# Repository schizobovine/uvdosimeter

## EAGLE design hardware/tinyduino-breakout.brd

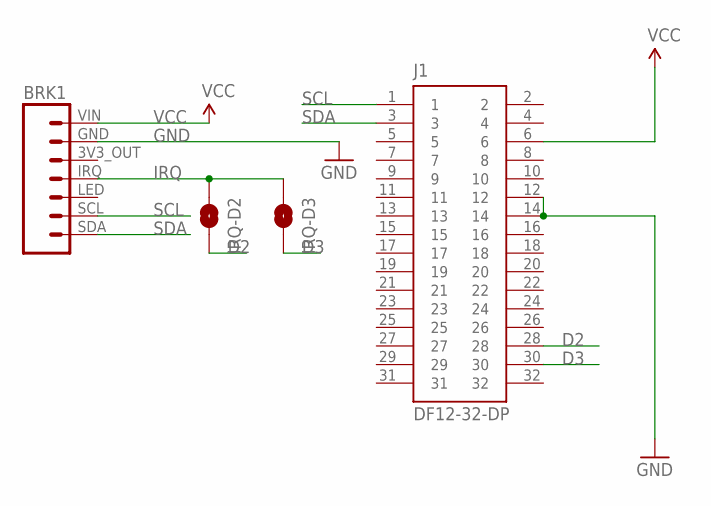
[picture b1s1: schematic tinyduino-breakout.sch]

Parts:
BRK1: ADAFRUIT-SI1145-BREAKOUT
IRQ-D2, IRQ-D3: JUMPER-PAD-2-NOYES_SILK; PAD-JUMPER-2-NO_YES_SILK
J1: DF12-32-DP

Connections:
D2: IRQ-D2.2, J1.28
D3: IRQ-D3.2, J1.30
GND: BRK1.GND, J1.12, J1.14
IRQ: BRK1.IRQ, IRQ-D2.1, IRQ-D3.1
SCL: BRK1.SCL, J1.1
SDA: BRK1.SDA, J1.3
VCC: BRK1.VIN, J1.6

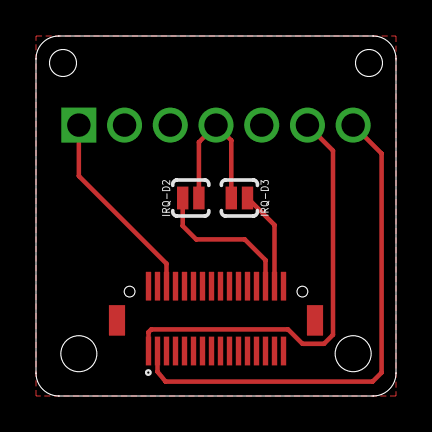
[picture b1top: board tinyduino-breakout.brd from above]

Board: 2 copper layers, 20.0 x 20.0 mm, 4 parts (1 on the bottom side), 7 nets.

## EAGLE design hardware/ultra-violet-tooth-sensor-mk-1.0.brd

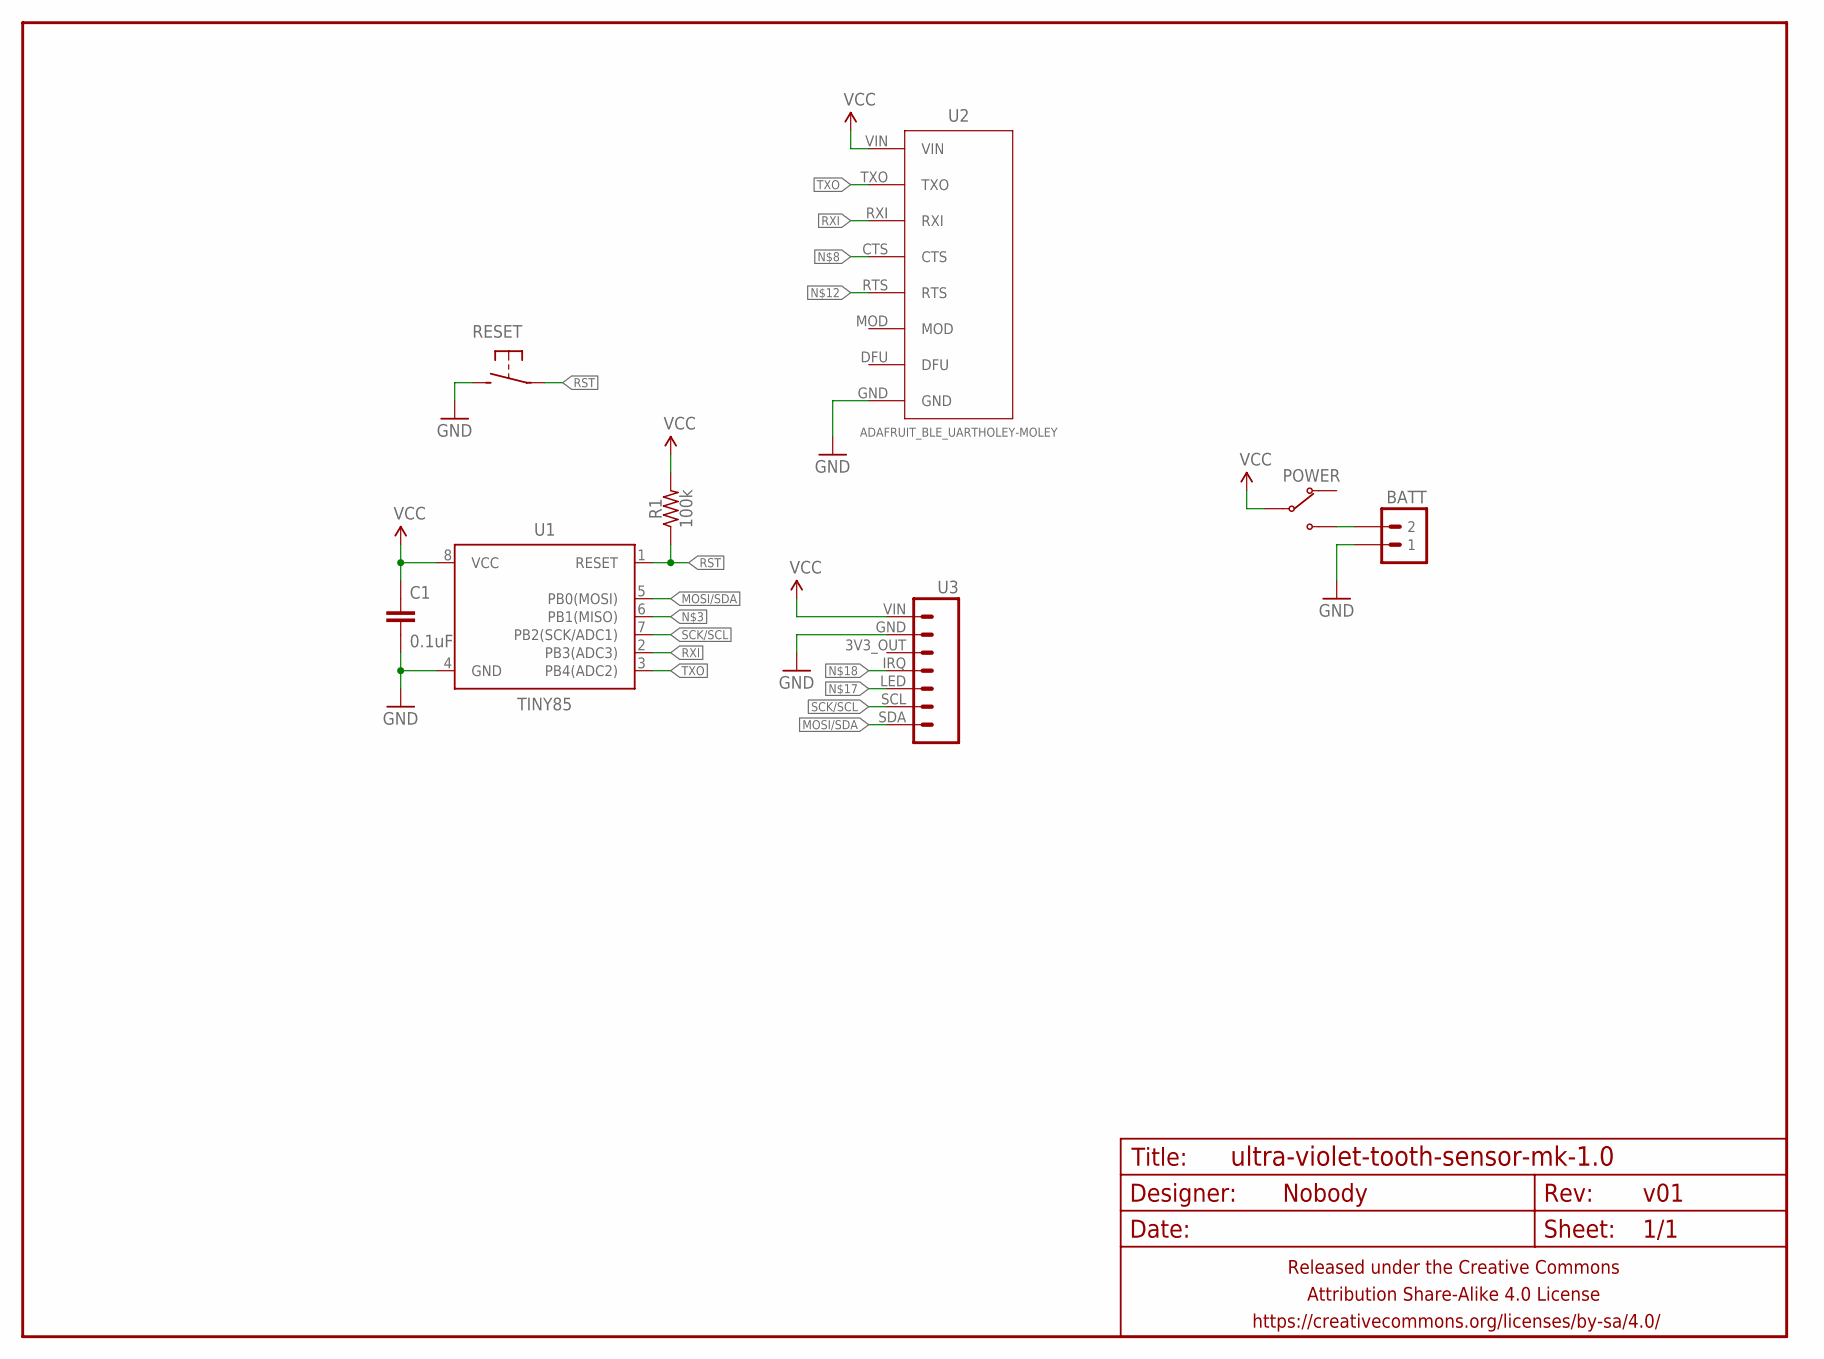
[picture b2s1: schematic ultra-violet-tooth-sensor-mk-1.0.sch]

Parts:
BATT: M02PTH-CENTERED-R+; 1X02-CENTER-R+
C1: 0.1uF; C025-024X044
FRAME1: FRAME-LETTERNO_PACKAGE; DUMMY
POWER: SWITCH-SPDTPTH-RA-2.54MM; SPDT-RA-2.54MM
R1: 100k; RESISTOR-AXIAL-PTH-7.62MM
RESET: SPST-NO-TACT3MM-RA; TACTILE-PTH-SIDE
U1: TINY85; DIP08
U2: ADAFRUIT_BLE_UARTHOLEY-MOLEY; ADAFRUIT_BLE_UART_HOLEY
U3: ADAFRUIT-SI1145-BREAKOUT

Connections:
GND: BATT.1, C1.2, RESET.2, U1.4 (GND), U2.GND, U3.GND
MOSI/SDA: U1.5 (PB0(MOSI)), U3.SDA
unnamed: BATT.2, POWER.3 (NO)
RST: R1.P$1 (1), RESET.1, U1.1 (RESET)
RXI: U1.2 (PB3(ADC3)), U2.RXI
SCK/SCL: U1.7 (PB2(SCK/ADC1)), U3.SCL
TXO: U1.3 (PB4(ADC2)), U2.TXO
VCC: C1.1, POWER.2 (COM), R1.P$2 (2), U1.8 (VCC), U2.VIN, U3.VIN

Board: 2 copper layers, 9 parts (2 on the bottom side), 8 nets, no tracks yet.

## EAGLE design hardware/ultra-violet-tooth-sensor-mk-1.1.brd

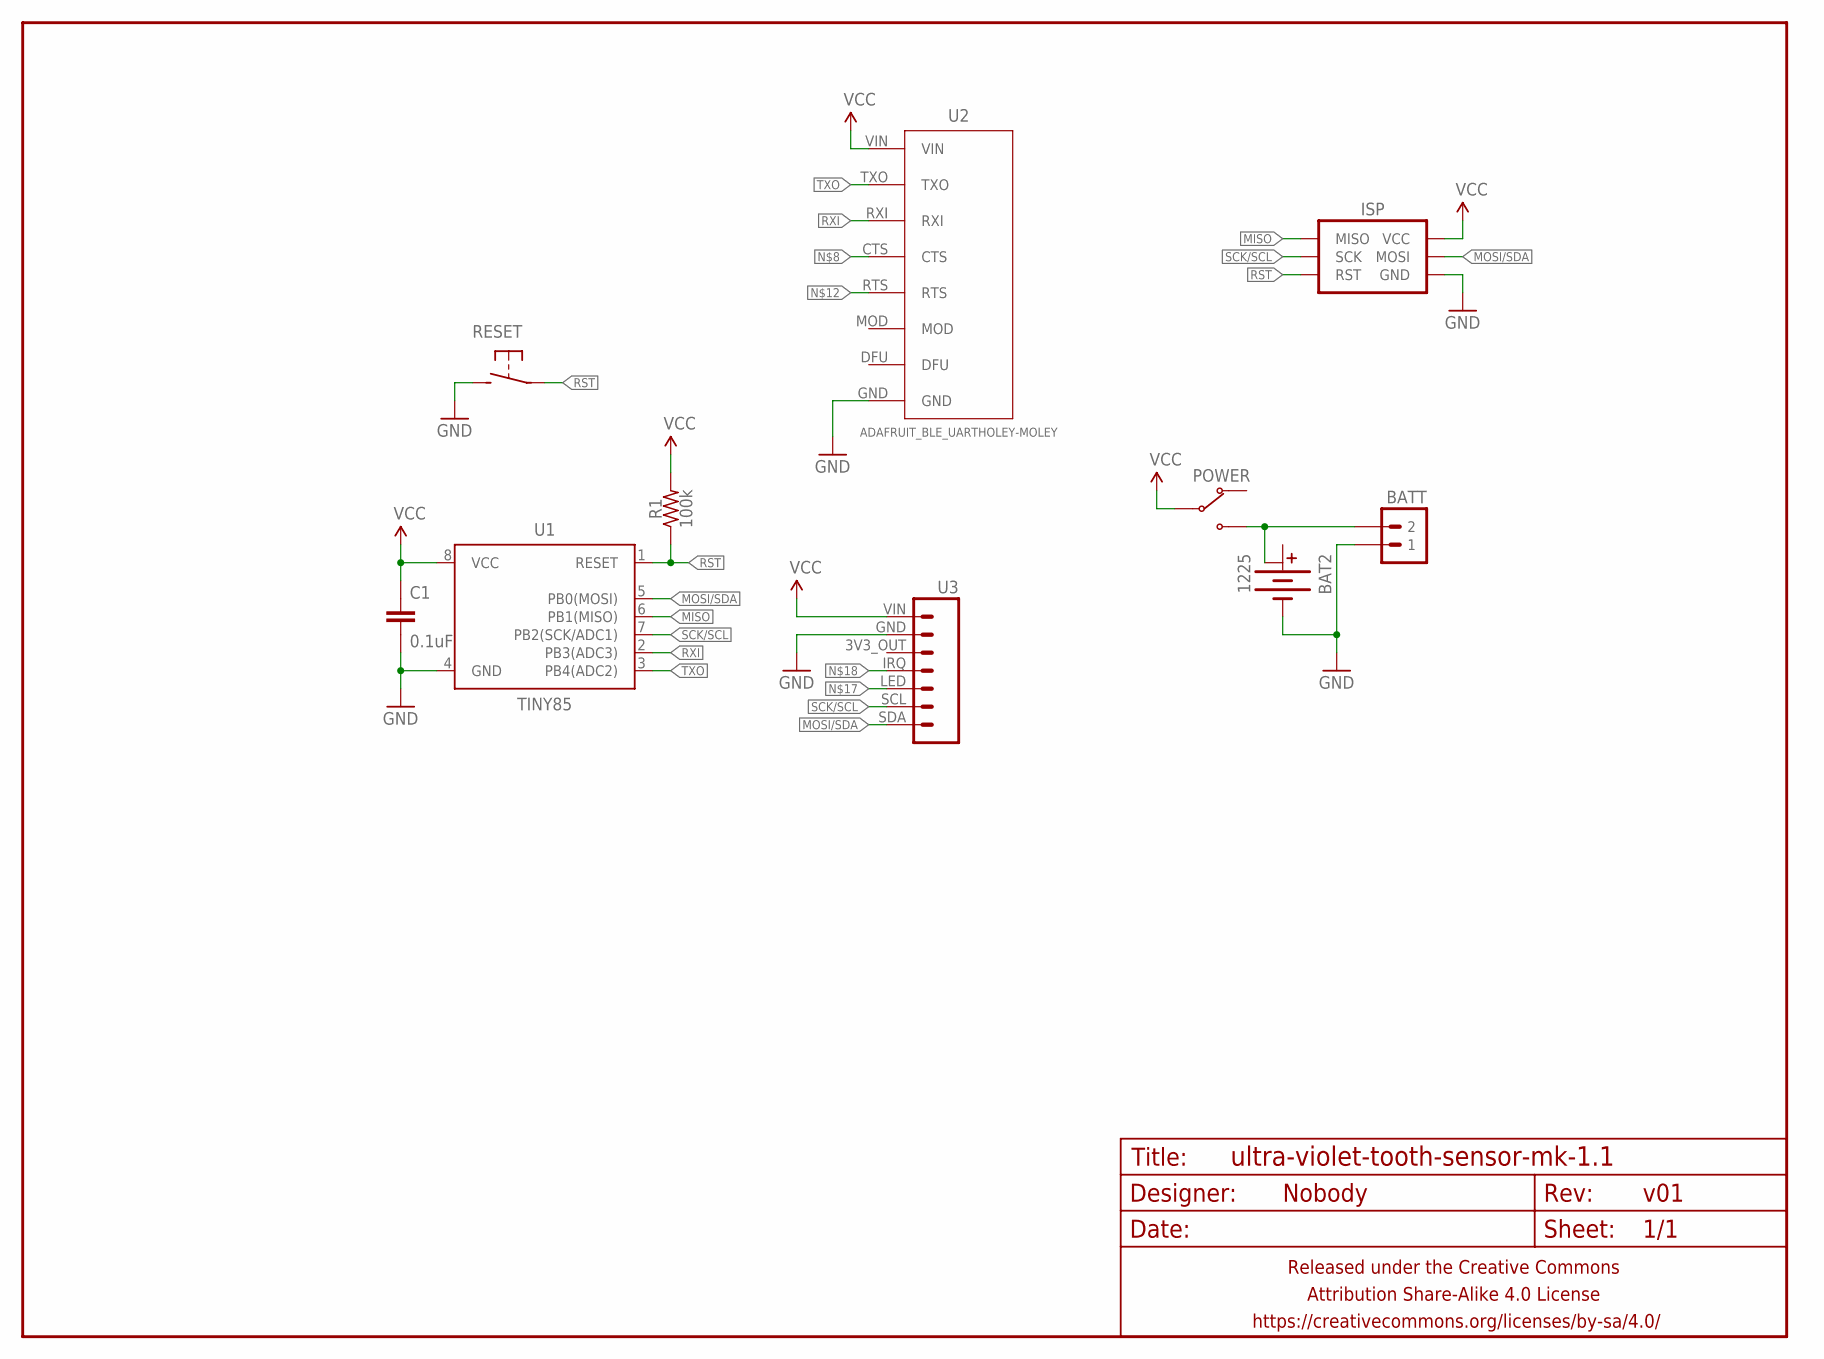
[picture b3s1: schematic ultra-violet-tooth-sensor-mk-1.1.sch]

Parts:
BAT2: 1225; BATTCON_12MM
BATT: M02PTH-CENTERED-R+; 1X02-CENTER-R+
C1: 0.1uF; C025-024X044
FRAME1: FRAME-LETTERNO_PACKAGE; DUMMY
ISP: AVR_SPI_PRG_6PTH; 2X3
POWER: SWITCH-SPDTPTH-RA-2.54MM; SPDT-RA-2.54MM
R1: 100k; RESISTOR-AXIAL-PTH-7.62MM
RESET: SPST-NO-TACT3MM-RA; TACTILE-PTH-SIDE
U1: TINY85; DIP08
U2: ADAFRUIT_BLE_UARTHOLEY-MOLEY; ADAFRUIT_BLE_UART_HOLEY
U3: ADAFRUIT-SI1145-BREAKOUT

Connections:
GND: BAT2.GND (-), BATT.1, C1.2, ISP.6 (GND), RESET.2, U1.4 (GND), U2.GND, U3.GND
MISO: ISP.1 (MISO), U1.6 (PB1(MISO))
MOSI/SDA: ISP.4 (MOSI), U1.5 (PB0(MOSI)), U3.SDA
unnamed: BAT2.PWR@2 (+1), BATT.2, POWER.3 (NO)
RST: ISP.5 (RST), R1.P$1 (1), RESET.1, U1.1 (RESET)
RXI: U1.2 (PB3(ADC3)), U2.RXI
SCK/SCL: ISP.3 (SCK), U1.7 (PB2(SCK/ADC1)), U3.SCL
TXO: U1.3 (PB4(ADC2)), U2.TXO
VCC: C1.1, ISP.2 (VCC), POWER.2 (COM), R1.P$2 (2), U1.8 (VCC), U2.VIN, U3.VIN

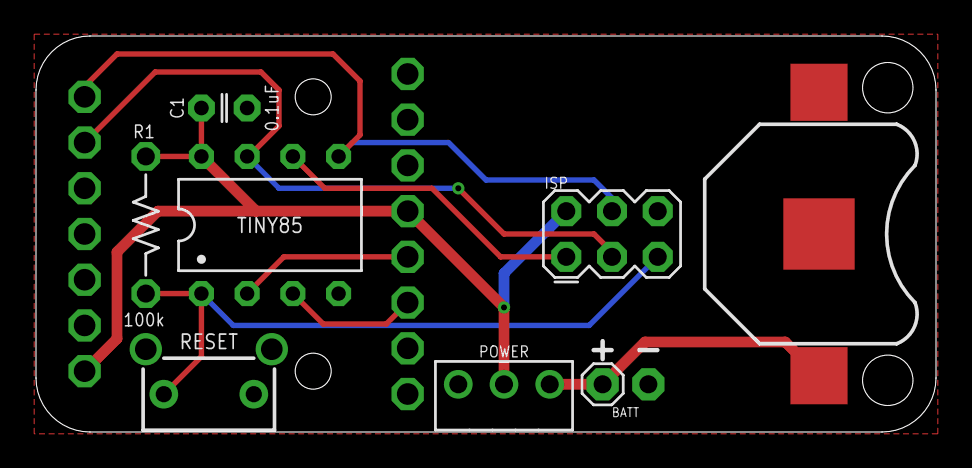
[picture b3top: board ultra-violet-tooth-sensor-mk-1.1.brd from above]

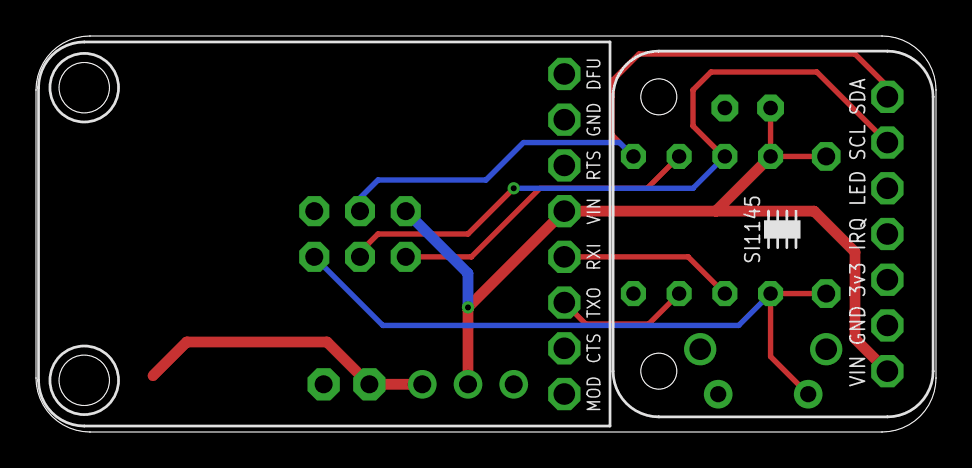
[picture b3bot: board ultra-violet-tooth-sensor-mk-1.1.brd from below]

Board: 2 copper layers, 50.0 x 22.0 mm, 11 parts (2 on the bottom side), 9 nets.

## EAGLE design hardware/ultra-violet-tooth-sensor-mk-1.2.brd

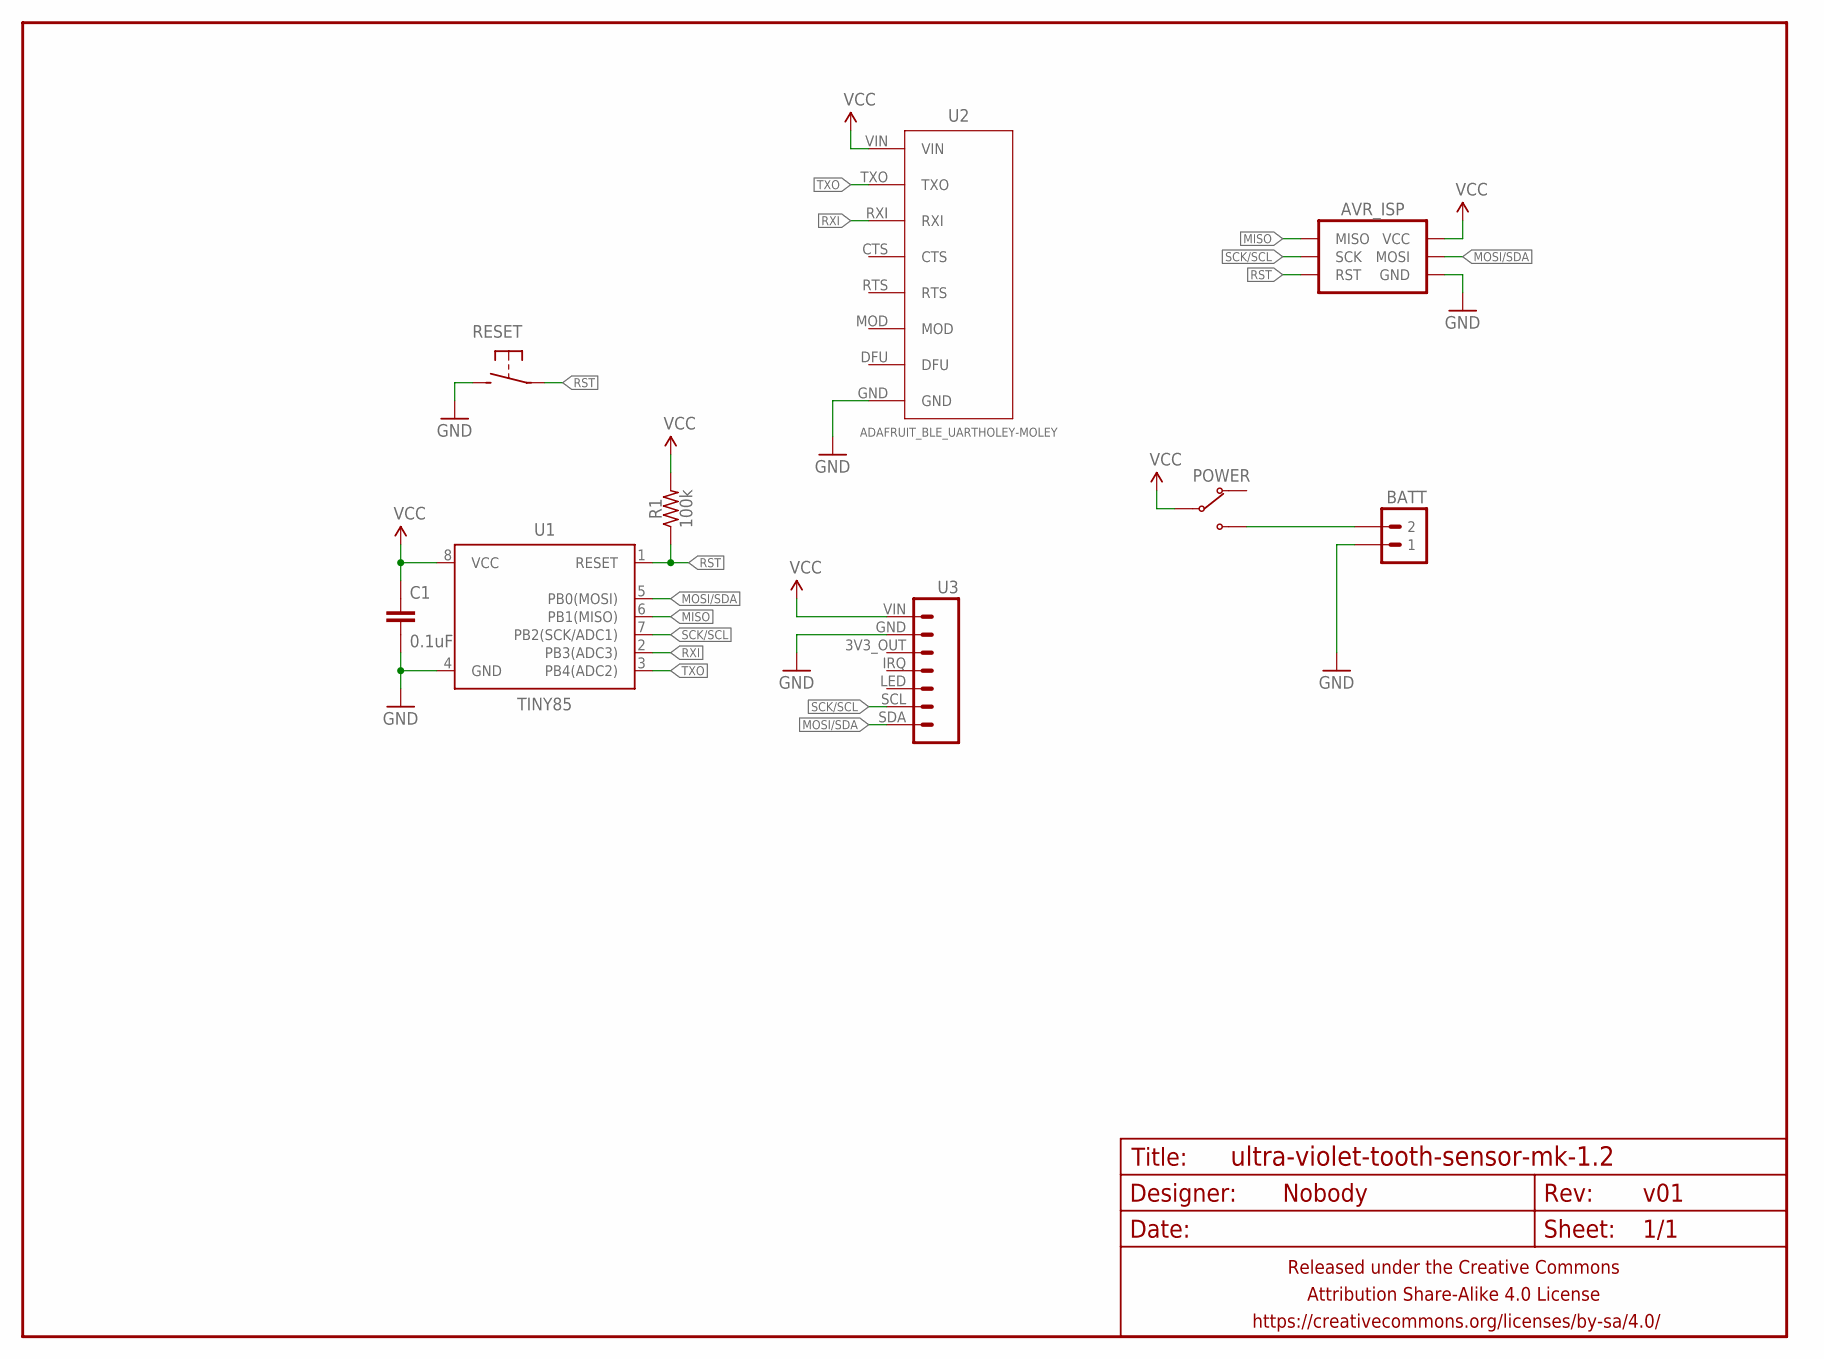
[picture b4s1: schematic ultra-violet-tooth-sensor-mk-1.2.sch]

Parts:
AVR_ISP: AVR_SPI_PRG_6PTH; 2X3
BATT: M02PTH-CENTERED-R+; 1X02-CENTER-R+
C1: 0.1uF; C025-024X044
FRAME1: FRAME-LETTERNO_PACKAGE; DUMMY
POWER: SWITCH-SPDTPTH-RA-2.54MM; SPDT-RA-2.54MM
R1: 100k; RESISTOR-AXIAL-PTH-6.35MM
RESET: SPST-NO-TACT3MM-RA; TACTILE-PTH-SIDE
U1: TINY85; DIP08
U2: ADAFRUIT_BLE_UARTHOLEY-MOLEY; ADAFRUIT_BLE_UART_HOLEY
U3: ADAFRUIT-SI1145-BREAKOUT

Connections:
GND: AVR_ISP.6 (GND), BATT.1, C1.2, RESET.2, U1.4 (GND), U2.GND, U3.GND
MISO: AVR_ISP.1 (MISO), U1.6 (PB1(MISO))
MOSI/SDA: AVR_ISP.4 (MOSI), U1.5 (PB0(MOSI)), U3.SDA
unnamed: BATT.2, POWER.3 (NO)
RST: AVR_ISP.5 (RST), R1.P$1 (1), RESET.1, U1.1 (RESET)
RXI: U1.2 (PB3(ADC3)), U2.RXI
SCK/SCL: AVR_ISP.3 (SCK), U1.7 (PB2(SCK/ADC1)), U3.SCL
TXO: U1.3 (PB4(ADC2)), U2.TXO
VCC: AVR_ISP.2 (VCC), C1.1, POWER.2 (COM), R1.P$2 (2), U1.8 (VCC), U2.VIN, U3.VIN

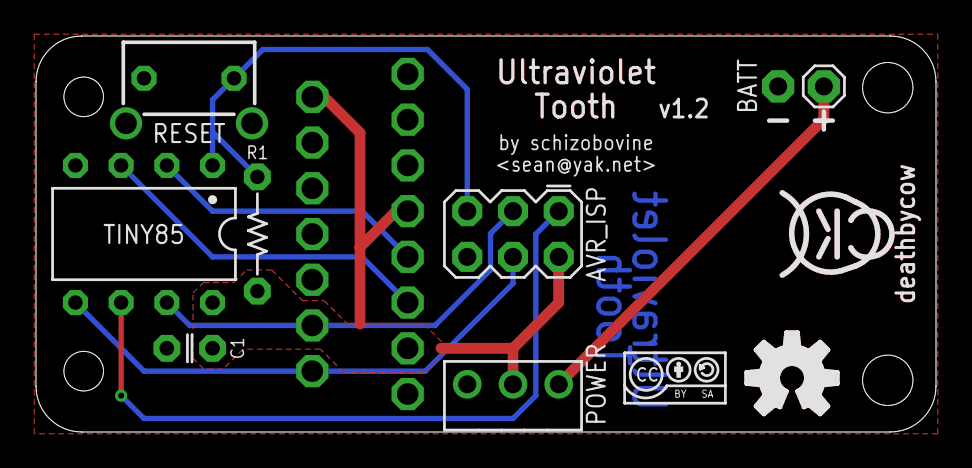
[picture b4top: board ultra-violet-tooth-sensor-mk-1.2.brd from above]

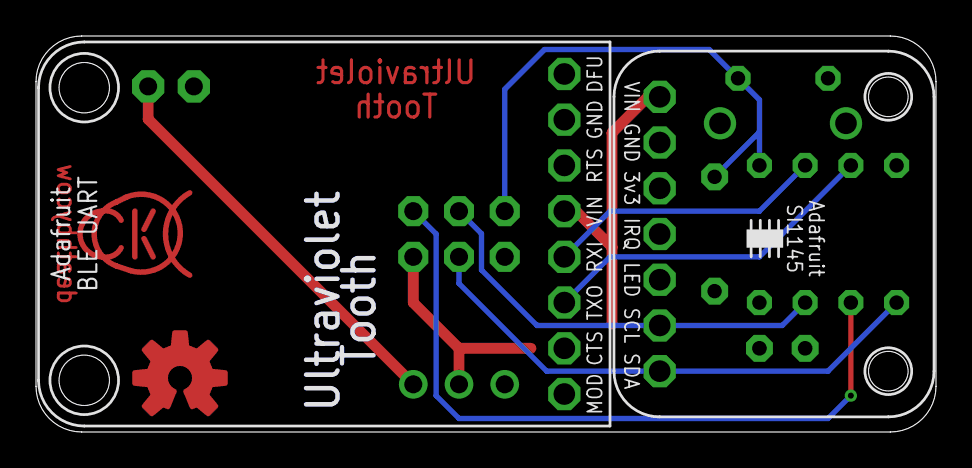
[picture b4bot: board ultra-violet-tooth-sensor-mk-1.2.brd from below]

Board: 2 copper layers, 50.0 x 22.0 mm, 13 parts (2 on the bottom side), 9 nets.

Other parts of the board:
U$1: CC-BY-SA-4.0-NO-URL
U$3: OSHWLOGO_TOP_0.2
U$4: COW_SMALL_METAL

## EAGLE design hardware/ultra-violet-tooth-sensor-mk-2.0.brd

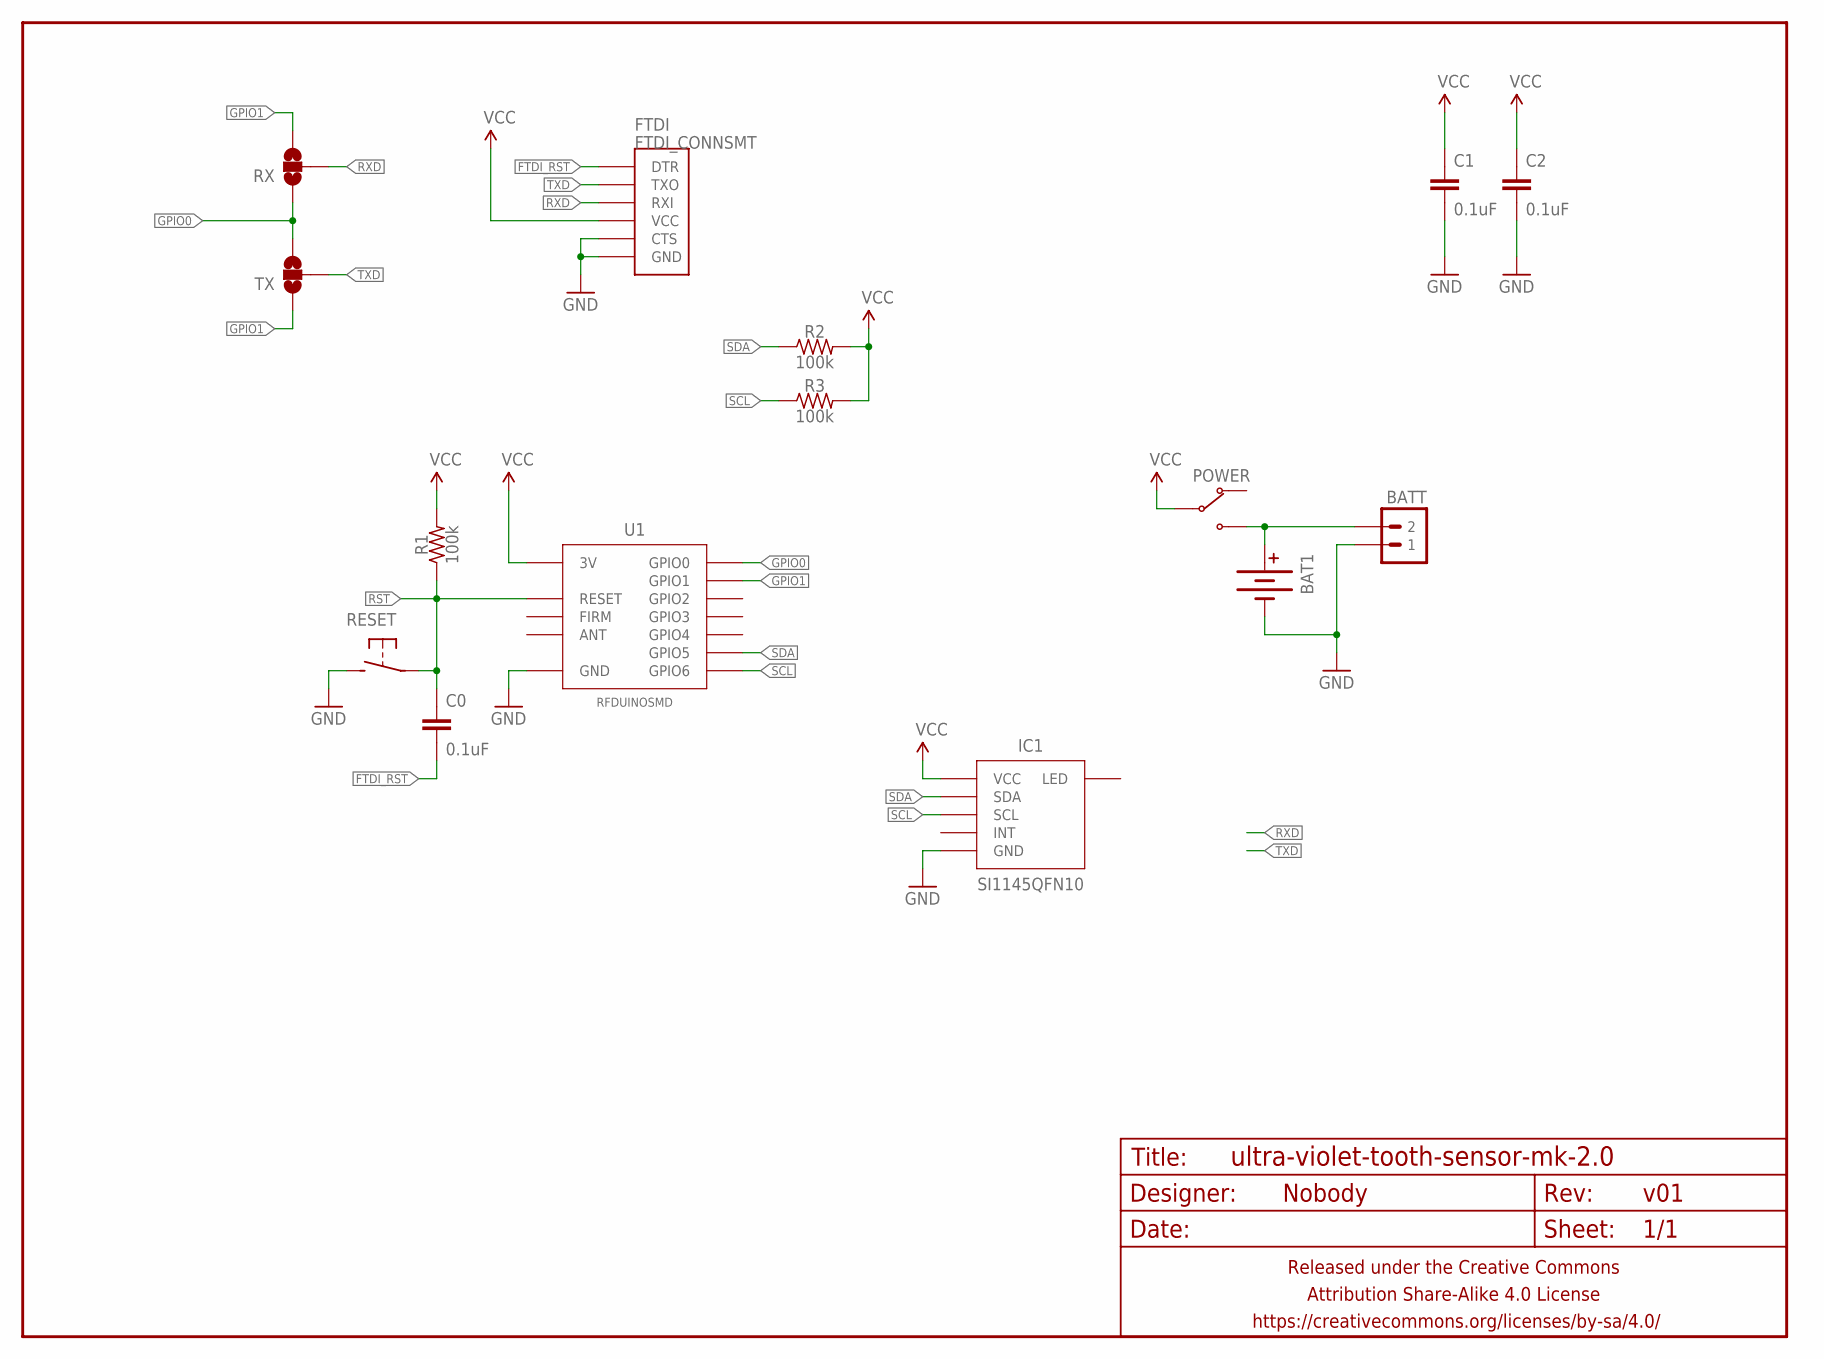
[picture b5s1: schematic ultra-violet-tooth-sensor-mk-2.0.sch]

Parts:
BAT1: BATTERY20MMSMD-MINE; BATTCON_20MM_MINE
BATT: M02PTH-CENTERED-R+; 1X02-CENTER-R+
C0, C1, C2: 0.1uF; C0805
FRAME1: FRAME-LETTERNO_PACKAGE; DUMMY
FTDI: FTDI_CONNSMT; FTDI_CONN_SMT
IC1: SI1145QFN10; SI1145
POWER: SWITCH-SPDTSMD-RA; SWITCH-SPDT-SMD-RA
R1, R2, R3: 100k; R0805
RESET: SPST-NO-TACTSMD-TINY; TACTILE-SWITCH-SMD
RX: JUMPER-PAD-3-NOFULL_BOX_SILK; PAD-JUMPER-3-NO_YES_SILK_FULL_BOX
TX: JUMPER-PAD-3-NOFULL_BOX_SILK; PAD-JUMPER-3-NO_YES_SILK_FULL_BOX
U1: RFDUINOSMD; RFDUINO-SMD

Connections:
FTDI_RST: C0.2, FTDI.DTR
GND: BAT1.BOTTOM (-), BATT.1, C1.2, C2.2, FTDI.CTS, FTDI.GND, IC1.GND, RESET.B@1 (2), RESET.B@2 (2), U1.GND@1 (GND), U1.GND@2 (GND), U1.GND@3 (GND), U1.GND@4 (GND), U1.GND@5 (GND), U1.GND@6 (GND), U1.GND@7 (GND), U1.GND@8 (GND)
GPIO0: RX.1, TX.3, U1.GPIO0
GPIO1: RX.3, TX.1, U1.GPIO1
unnamed: BAT1.TOP@1 (+), BAT1.TOP@2 (+), BATT.2, POWER.1 (NO)
RST: C0.1, R1.1, RESET.A@1 (1), RESET.A@2 (1), U1.RESET
RXD: FTDI.RXI, RX.2
SCL: IC1.SCL, R3.1, U1.GPIO6
SDA: IC1.SDA, R2.1, U1.GPIO5
TXD: FTDI.TXO, TX.2
VCC: C1.1, C2.1, FTDI.VCC, IC1.VCC@1 (VCC), IC1.VCC@2 (VCC), IC1.VCC@3 (VCC), POWER.2 (COM), R1.2, R2.2, R3.2, U1.3V

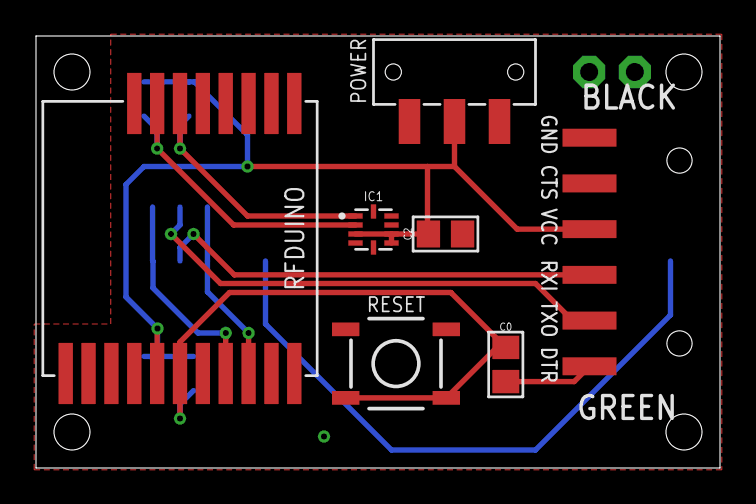
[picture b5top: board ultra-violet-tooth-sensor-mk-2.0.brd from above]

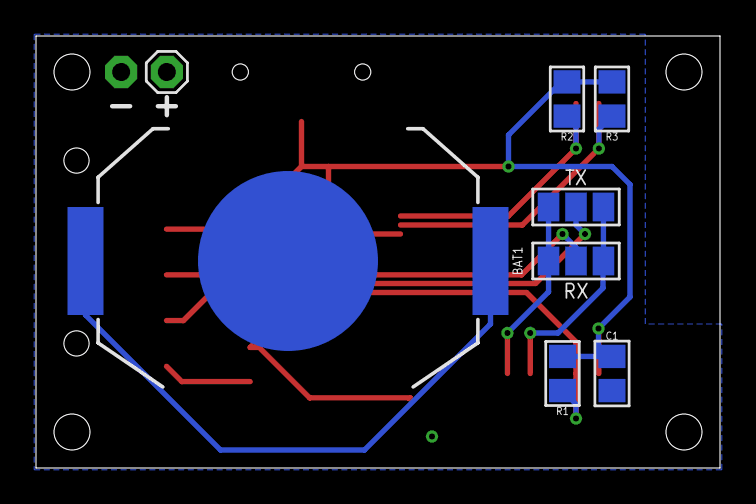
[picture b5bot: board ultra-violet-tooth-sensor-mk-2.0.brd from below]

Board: 2 copper layers, 38.0 x 24.0 mm, 19 parts (8 on the bottom side), 11 nets.

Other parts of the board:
U$1: CC-BY-SA-4.0-NO-URL
U$3: OSHWLOGO_TOP_0.2
U$4: COW_SMALL_METAL

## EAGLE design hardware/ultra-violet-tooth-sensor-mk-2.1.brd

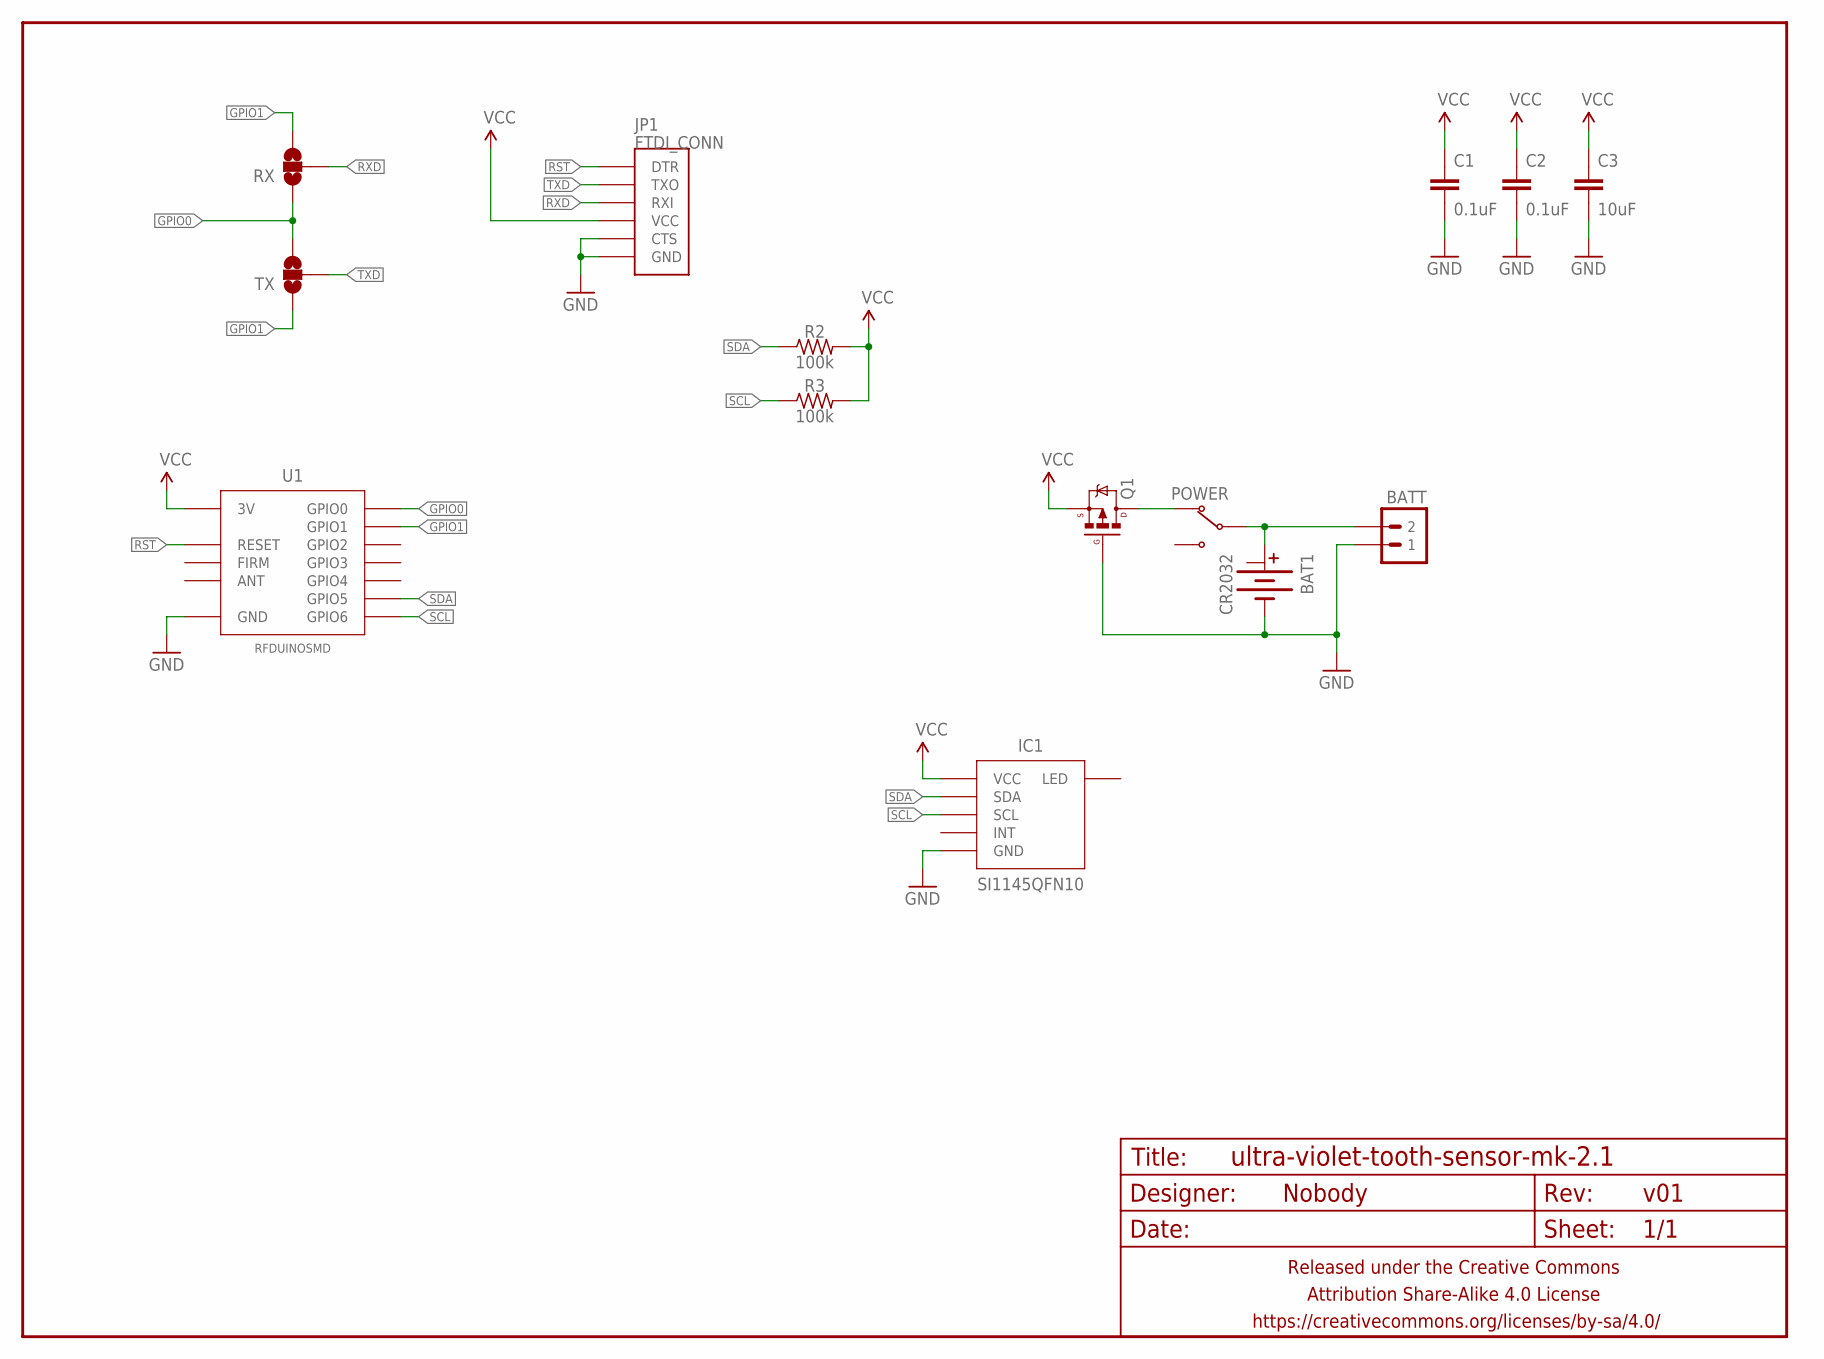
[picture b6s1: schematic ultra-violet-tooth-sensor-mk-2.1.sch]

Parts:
BAT1: CR2032; BATTCON_20MM_MINE_STAHPIT
BATT: M02PTH-CENTERED-R+; 1X02-CENTER-R+
C1, C2: 0.1uF; C0805
C3: 10uF; C1206
FRAME1: FRAME-LETTERNO_PACKAGE; DUMMY
IC1: SI1145QFN10; SI1145
JP1: FTDI_CONN
POWER: SWITCH-SPDTPTH-RA-2.54MM; SPDT-RA-2.54MM
Q1: MOSFET-PCHANNELIRLML2244; SOT23-3
R2, R3: 100k; R0805
RX: JUMPER-PAD-3-NOFULL_BOX_SILK; PAD-JUMPER-3-NO_YES_SILK_FULL_BOX
TX: JUMPER-PAD-3-NOFULL_BOX_SILK; PAD-JUMPER-3-NO_YES_SILK_FULL_BOX
U1: RFDUINOSMD; RFDUINO-SMD

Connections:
GND: BAT1.BOTTOM (-), BATT.1, C1.2, C2.2, C3.2, IC1.GND, JP1.CTS, JP1.GND, Q1.1 (G), U1.GND@1 (GND), U1.GND@2 (GND), U1.GND@3 (GND), U1.GND@4 (GND), U1.GND@5 (GND), U1.GND@6 (GND), U1.GND@7 (GND), U1.GND@8 (GND)
GPIO0: RX.1, TX.3, U1.GPIO0
GPIO1: RX.3, TX.1, U1.GPIO1
unnamed: BAT1.TOP@1 (+), BATT.2, POWER.2 (COM)
unnamed: POWER.1 (NC), Q1.3 (D)
RST: JP1.DTR, U1.RESET
RXD: JP1.RXI, RX.2
SCL: IC1.SCL, R3.1, U1.GPIO6
SDA: IC1.SDA, R2.1, U1.GPIO5
TXD: JP1.TXO, TX.2
VCC: C1.1, C2.1, C3.1, IC1.VCC@1 (VCC), IC1.VCC@2 (VCC), IC1.VCC@3 (VCC), JP1.VCC, Q1.2 (S), R2.2, R3.2, U1.3V

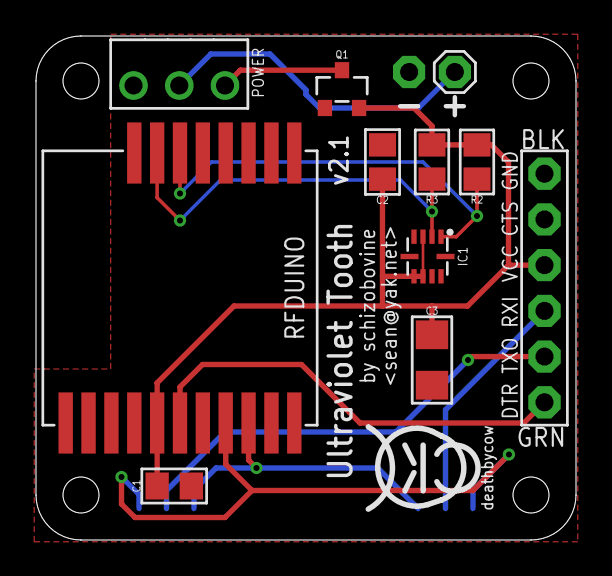
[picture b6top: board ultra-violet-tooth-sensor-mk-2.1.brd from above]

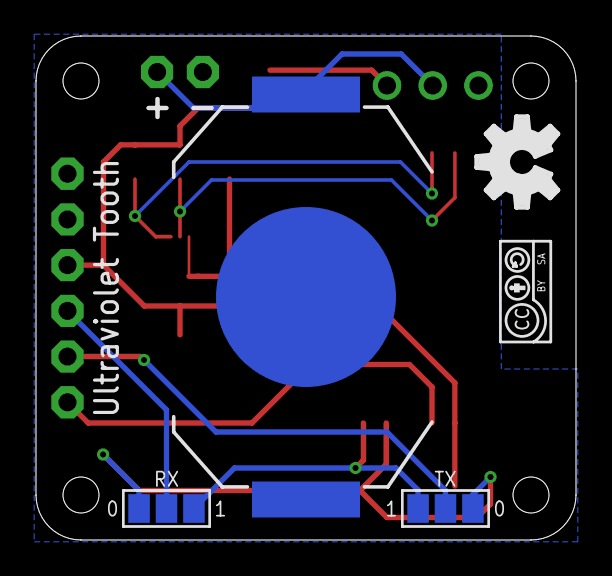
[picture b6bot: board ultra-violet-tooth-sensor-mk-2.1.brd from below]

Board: 2 copper layers, 30.0 x 28.0 mm, 18 parts (5 on the bottom side), 11 nets.

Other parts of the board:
U$1: CC-BY-SA-4.0-NO-URL
U$5: COW_SMALL
U$6: OSHWLOGO_SILKONLY

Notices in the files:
parts and their libraries:
SparkFun-Aesthetics: Licensing: Creative Commons ShareAlike 4.0 International - https://creativecommons.org/licenses/by-sa/4.0
A_butts: Released under the Creative Commons Attribution Share-Alike 4.0 License
A_butts: https://creativecommons.org/licenses/by-sa/4.0
